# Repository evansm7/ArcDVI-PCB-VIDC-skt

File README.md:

# ArcDVI VIDC socket interposer PCB

Kicad 6.0 PCB design for the ArcDVI VIDC socket interposer board:

This board carries a PLCC68 socket on top, and PLCC68 plug on bottom.  It plugs into VIDC's socket on an Archimedes A440-like machine, with VIDC moved to the socket on top, and exports the buffered signals over FFC to the ArcDVI main PCB.

See <https://stardot.org.uk> for more info.

# License

ArcDVI is copyright 2023 Matt Evans.

This work is licensed under the Creative Commons Attribution-NonCommercial-ShareAlike 3.0 Unported License. To view a copy of this license, visit http://creativecommons.org/licenses/by-nc-sa/3.0/ or send a letter to Creative Commons, PO Box 1866, Mountain View, CA 94042, USA.

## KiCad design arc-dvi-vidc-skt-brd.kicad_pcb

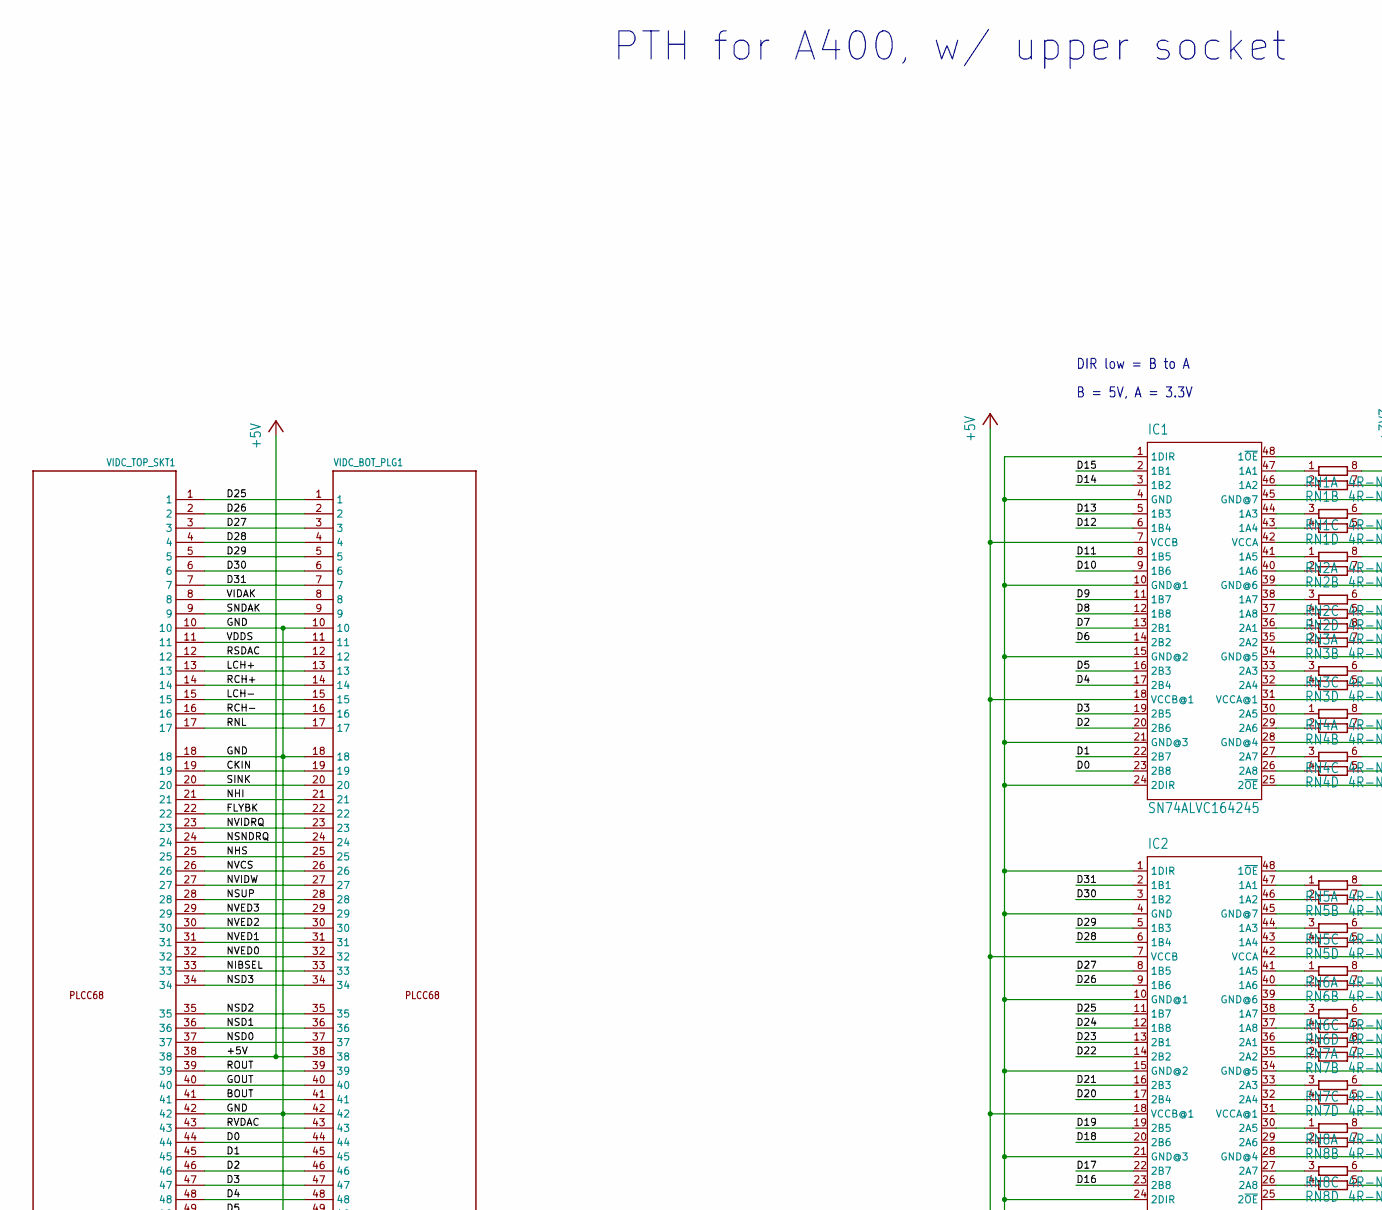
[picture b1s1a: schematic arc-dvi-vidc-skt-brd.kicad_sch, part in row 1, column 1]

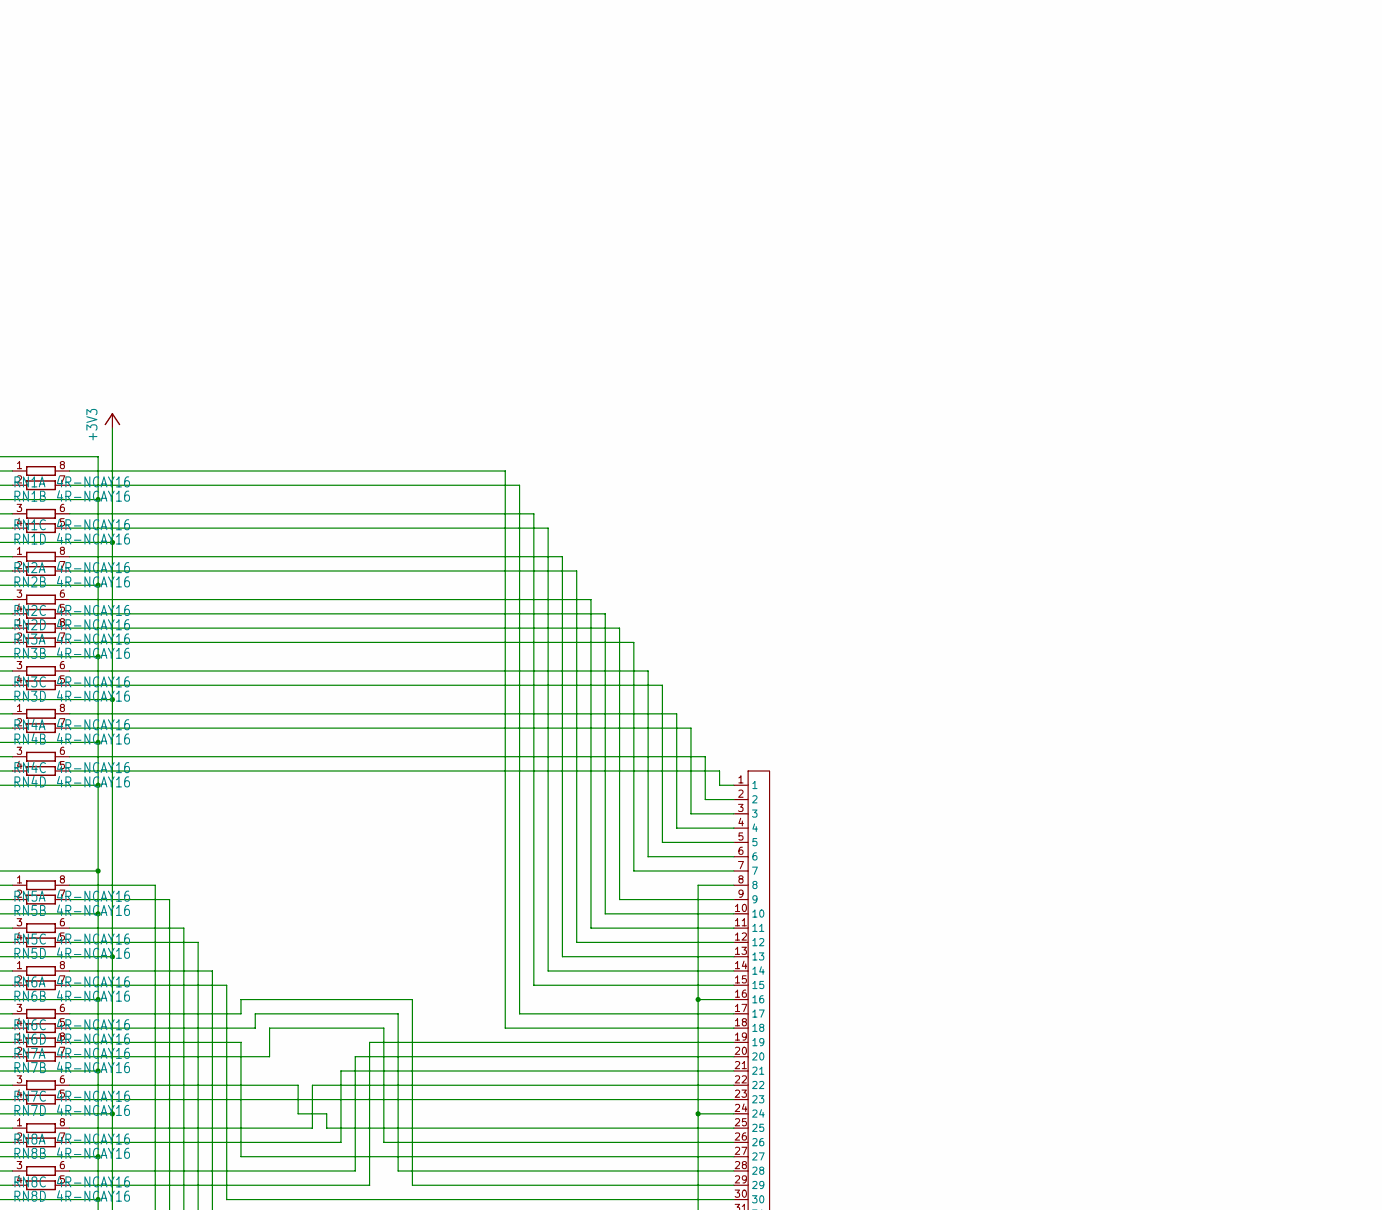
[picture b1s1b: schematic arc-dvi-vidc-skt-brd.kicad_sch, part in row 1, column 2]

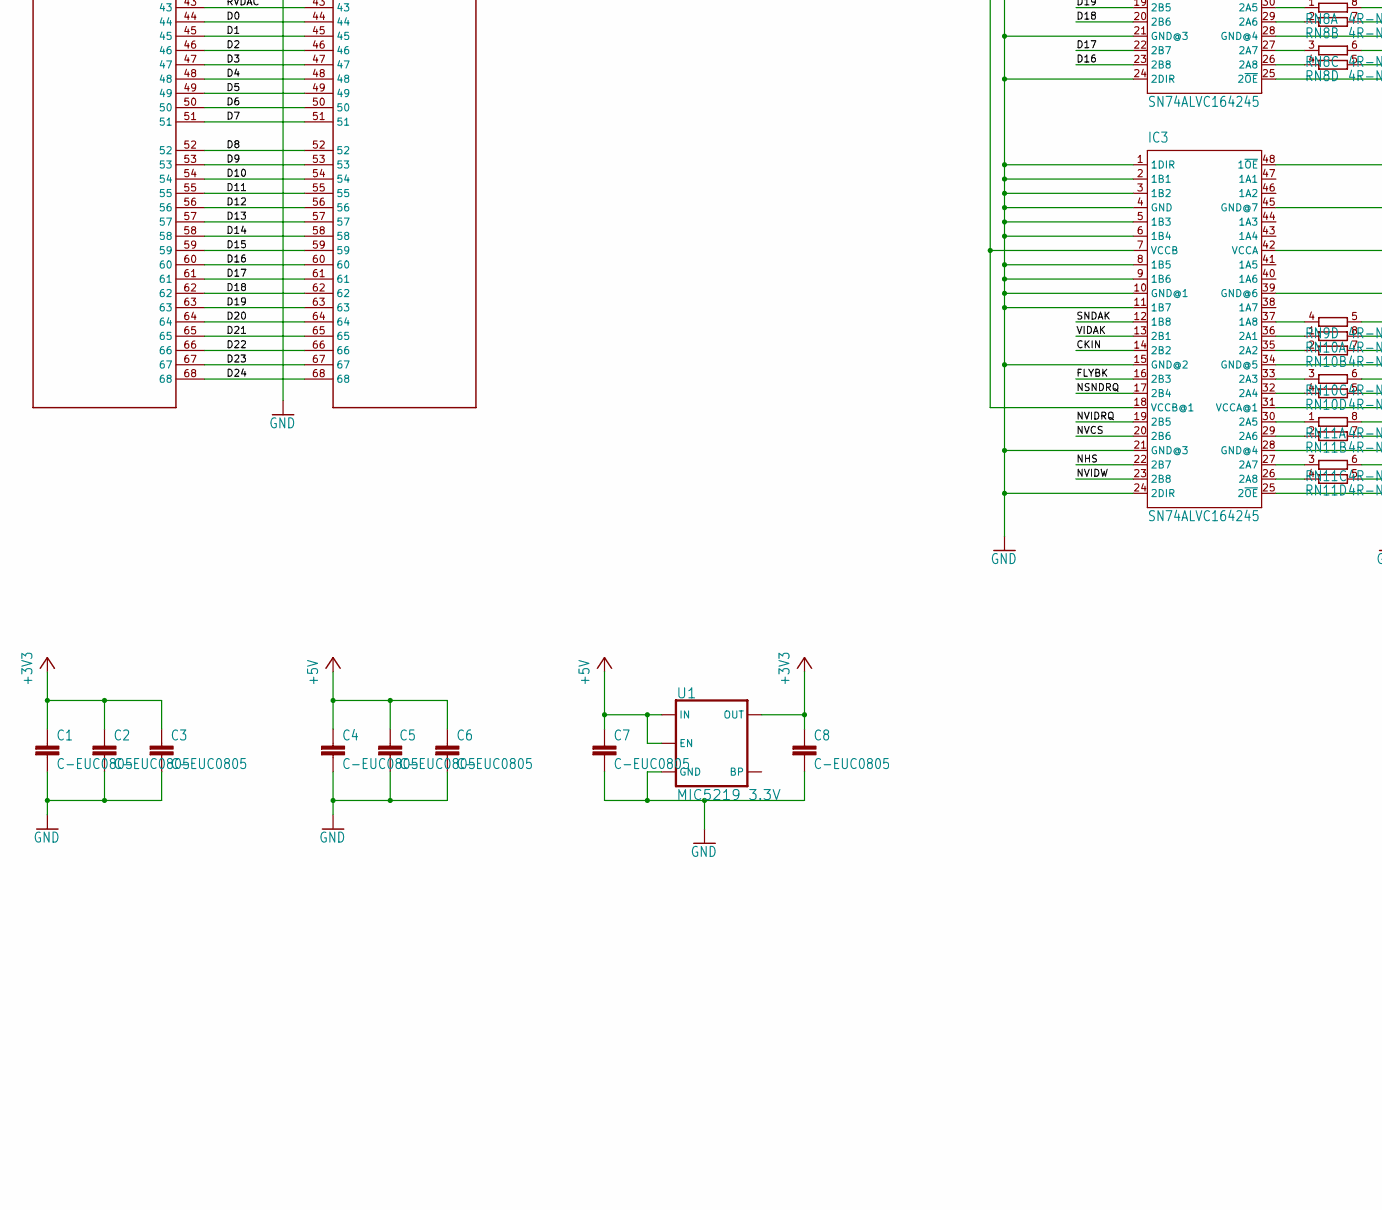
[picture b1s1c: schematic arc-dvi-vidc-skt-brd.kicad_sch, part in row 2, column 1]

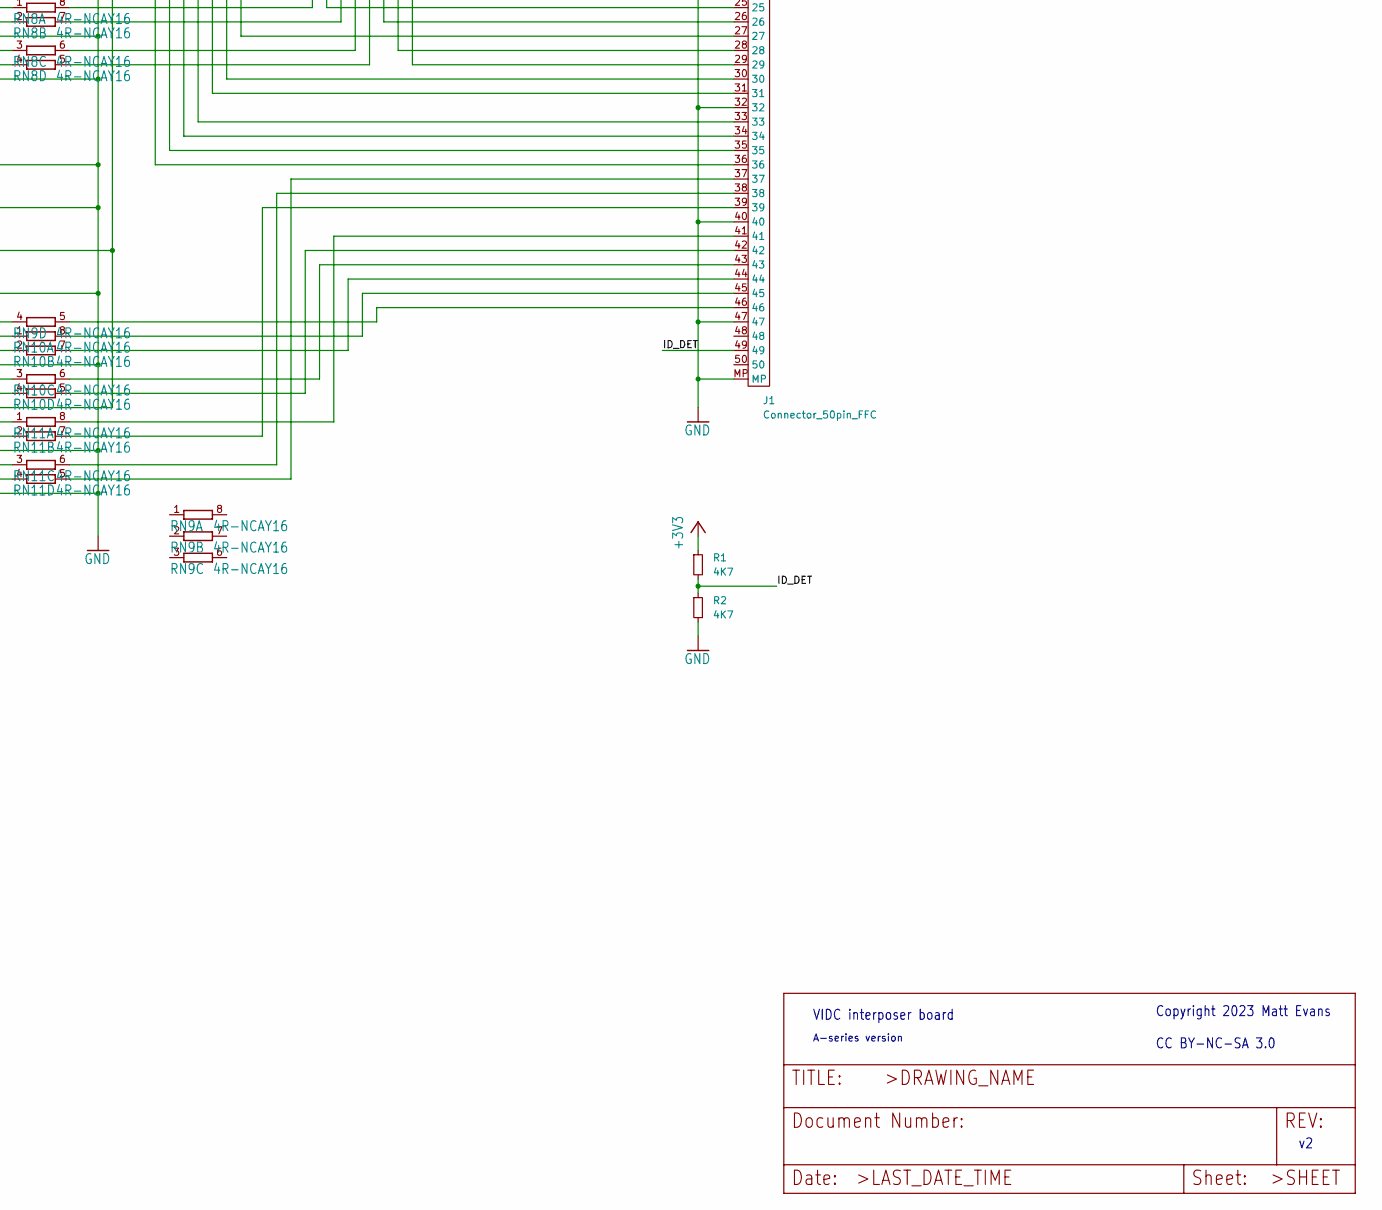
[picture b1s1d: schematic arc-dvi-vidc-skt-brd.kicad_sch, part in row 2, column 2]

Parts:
C1, C2, C3, C4, C5, C6, C7, C8: C-EUC0805; C_0805_2012Metric_Pad1.18x1.45mm_HandSolder
IC1, IC2, IC3: SN74ALVC164245; TSSOP-48_6.1x12.5mm_P0.5mm
J1: Connector_50pin_FFC; Hirose_FH12-50S-0.5SH_1x50-1MP_P0.50mm_Horizontal
R1, R2: 4K7; R_0603_1608Metric
RN1, RN2, RN3, RN4, RN5, RN6, RN7, RN8, RN9, RN10, RN11: 4R-NCAY16; R_Array_Convex_4x0603
U1: MIC5219 3.3V; SOT-23-5
VIDC_BOT_PLG1: RAW_PLCC68PTH; PLCC68-plug-wide
VIDC_TOP_SKT1: RAW_PLCC68PTH; PLCC-68_SMD-Socket

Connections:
+3V3: C1.1, C2.1, C3.1, C8.1, IC1.31 (VCCA@1), IC1.42 (VCCA), IC2.31 (VCCA@1), IC2.42 (VCCA), IC3.31 (VCCA@1), IC3.42 (VCCA), R1.1, U1.5 (OUT)
+5V: C4.1, C5.1, C6.1, C7.1, IC1.7 (VCCB), IC1.18 (VCCB@1), IC2.7 (VCCB), IC2.18 (VCCB@1), IC3.7 (VCCB), IC3.18 (VCCB@1), U1.1 (IN), U1.3 (EN), VIDC_BOT_PLG1.38, VIDC_TOP_SKT1.38
/BOUT: VIDC_BOT_PLG1.41, VIDC_TOP_SKT1.41
/CKIN: IC3.14 (2B2), VIDC_BOT_PLG1.19, VIDC_TOP_SKT1.19
/D0: IC1.23 (2B8), VIDC_BOT_PLG1.44, VIDC_TOP_SKT1.44
/D1: IC1.22 (2B7), VIDC_BOT_PLG1.45, VIDC_TOP_SKT1.45
/D2: IC1.20 (2B6), VIDC_BOT_PLG1.46, VIDC_TOP_SKT1.46
/D3: IC1.19 (2B5), VIDC_BOT_PLG1.47, VIDC_TOP_SKT1.47
/D4: IC1.17 (2B4), VIDC_BOT_PLG1.48, VIDC_TOP_SKT1.48
/D5: IC1.16 (2B3), VIDC_BOT_PLG1.49, VIDC_TOP_SKT1.49
/D6: IC1.14 (2B2), VIDC_BOT_PLG1.50, VIDC_TOP_SKT1.50
/D7: IC1.13 (2B1), VIDC_BOT_PLG1.51, VIDC_TOP_SKT1.51
/D8: IC1.12 (1B8), VIDC_BOT_PLG1.52, VIDC_TOP_SKT1.52
/D9: IC1.11 (1B7), VIDC_BOT_PLG1.53, VIDC_TOP_SKT1.53
/D10: IC1.9 (1B6), VIDC_BOT_PLG1.54, VIDC_TOP_SKT1.54
/D11: IC1.8 (1B5), VIDC_BOT_PLG1.55, VIDC_TOP_SKT1.55
/D12: IC1.6 (1B4), VIDC_BOT_PLG1.56, VIDC_TOP_SKT1.56
/D13: IC1.5 (1B3), VIDC_BOT_PLG1.57, VIDC_TOP_SKT1.57
/D14: IC1.3 (1B2), VIDC_BOT_PLG1.58, VIDC_TOP_SKT1.58
/D15: IC1.2 (1B1), VIDC_BOT_PLG1.59, VIDC_TOP_SKT1.59
/D16: IC2.23 (2B8), VIDC_BOT_PLG1.60, VIDC_TOP_SKT1.60
/D17: IC2.22 (2B7), VIDC_BOT_PLG1.61, VIDC_TOP_SKT1.61
/D18: IC2.20 (2B6), VIDC_BOT_PLG1.62, VIDC_TOP_SKT1.62
/D19: IC2.19 (2B5), VIDC_BOT_PLG1.63, VIDC_TOP_SKT1.63
/D20: IC2.17 (2B4), VIDC_BOT_PLG1.64, VIDC_TOP_SKT1.64
/D21: IC2.16 (2B3), VIDC_BOT_PLG1.65, VIDC_TOP_SKT1.65
/D22: IC2.14 (2B2), VIDC_BOT_PLG1.66, VIDC_TOP_SKT1.66
/D23: IC2.13 (2B1), VIDC_BOT_PLG1.67, VIDC_TOP_SKT1.67
/D24: IC2.12 (1B8), VIDC_BOT_PLG1.68, VIDC_TOP_SKT1.68
/D25: IC2.11 (1B7), VIDC_BOT_PLG1.1, VIDC_TOP_SKT1.1
/D26: IC2.9 (1B6), VIDC_BOT_PLG1.2, VIDC_TOP_SKT1.2
/D27: IC2.8 (1B5), VIDC_BOT_PLG1.3, VIDC_TOP_SKT1.3
/D28: IC2.6 (1B4), VIDC_BOT_PLG1.4, VIDC_TOP_SKT1.4
/D29: IC2.5 (1B3), VIDC_BOT_PLG1.5, VIDC_TOP_SKT1.5
/D30: IC2.3 (1B2), VIDC_BOT_PLG1.6, VIDC_TOP_SKT1.6
/D31: IC2.2 (1B1), VIDC_BOT_PLG1.7, VIDC_TOP_SKT1.7
/FLYBK: IC3.16 (2B3), VIDC_BOT_PLG1.22, VIDC_TOP_SKT1.22
/GOUT: VIDC_BOT_PLG1.40, VIDC_TOP_SKT1.40
/ID_DET: J1.49, R1.2, R2.1
/LCH+: VIDC_BOT_PLG1.13, VIDC_TOP_SKT1.13
/LCH-: VIDC_BOT_PLG1.15, VIDC_TOP_SKT1.15
/NHI: VIDC_BOT_PLG1.21, VIDC_TOP_SKT1.21
/NHS: IC3.22 (2B7), VIDC_BOT_PLG1.25, VIDC_TOP_SKT1.25
/NIBSEL: VIDC_BOT_PLG1.33, VIDC_TOP_SKT1.33
/NSD0: VIDC_BOT_PLG1.37, VIDC_TOP_SKT1.37
/NSD1: VIDC_BOT_PLG1.36, VIDC_TOP_SKT1.36
/NSD2: VIDC_BOT_PLG1.35, VIDC_TOP_SKT1.35
/NSD3: VIDC_BOT_PLG1.34, VIDC_TOP_SKT1.34
/NSNDRQ: IC3.17 (2B4), VIDC_BOT_PLG1.24, VIDC_TOP_SKT1.24
/NSUP: VIDC_BOT_PLG1.28, VIDC_TOP_SKT1.28
/NVCS: IC3.20 (2B6), VIDC_BOT_PLG1.26, VIDC_TOP_SKT1.26
/NVED0: VIDC_BOT_PLG1.32, VIDC_TOP_SKT1.32
/NVED1: VIDC_BOT_PLG1.31, VIDC_TOP_SKT1.31
/NVED2: VIDC_BOT_PLG1.30, VIDC_TOP_SKT1.30
/NVED3: VIDC_BOT_PLG1.29, VIDC_TOP_SKT1.29
/NVIDRQ: IC3.19 (2B5), VIDC_BOT_PLG1.23, VIDC_TOP_SKT1.23
/NVIDW: IC3.23 (2B8), VIDC_BOT_PLG1.27, VIDC_TOP_SKT1.27
/RCH+: VIDC_BOT_PLG1.14, VIDC_TOP_SKT1.14
/RCH-: VIDC_BOT_PLG1.16, VIDC_TOP_SKT1.16
/RNL: VIDC_BOT_PLG1.17, VIDC_TOP_SKT1.17
/ROUT: VIDC_BOT_PLG1.39, VIDC_TOP_SKT1.39
/RSDAC: VIDC_BOT_PLG1.12, VIDC_TOP_SKT1.12
/RVDAC: VIDC_BOT_PLG1.43, VIDC_TOP_SKT1.43
/SINK: VIDC_BOT_PLG1.20, VIDC_TOP_SKT1.20
/SNDAK: IC3.12 (1B8), VIDC_BOT_PLG1.9, VIDC_TOP_SKT1.9
/VDDS: VIDC_BOT_PLG1.11, VIDC_TOP_SKT1.11
/VIDAK: IC3.13 (2B1), VIDC_BOT_PLG1.8, VIDC_TOP_SKT1.8
GND: C1.2, C2.2, C3.2, C4.2, C5.2, C6.2, C7.2, C8.2, IC1.1 (1DIR), IC1.4 (GND), IC1.10 (GND@1), IC1.15 (GND@2), IC1.21 (GND@3), IC1.24 (2DIR), IC1.25 (2~OE), IC1.28 (GND@4), IC1.34 (GND@5), IC1.39 (GND@6), IC1.45 (GND@7), IC1.48 (1~OE), IC2.1 (1DIR), IC2.4 (GND), IC2.10 (GND@1), IC2.15 (GND@2), IC2.21 (GND@3), IC2.24 (2DIR), IC2.25 (2~OE), IC2.28 (GND@4), IC2.34 (GND@5), IC2.39 (GND@6), IC2.45 (GND@7), IC2.48 (1~OE), IC3.1 (1DIR), IC3.2 (1B1), IC3.3 (1B2), IC3.4 (GND), IC3.5 (1B3), IC3.6 (1B4), IC3.8 (1B5), IC3.9 (1B6), IC3.10 (GND@1), IC3.11 (1B7), IC3.15 (GND@2), IC3.21 (GND@3), IC3.24 (2DIR), IC3.25 (2~OE), IC3.28 (GND@4), IC3.34 (GND@5), IC3.39 (GND@6), IC3.45 (GND@7), IC3.48 (1~OE), J1.8, J1.16, J1.24, J1.32, J1.40, J1.47, J1.MP, R2.2, U1.2 (GND), VIDC_BOT_PLG1.10, VIDC_BOT_PLG1.18, VIDC_BOT_PLG1.42, VIDC_TOP_SKT1.10, VIDC_TOP_SKT1.18, VIDC_TOP_SKT1.42
unnamed: IC1.26 (2A8), RN4.4 (1)
unnamed: IC1.27 (2A7), RN4.3 (1)
unnamed: IC1.29 (2A6), RN4.2 (1)
unnamed: IC1.30 (2A5), RN4.1
unnamed: IC1.32 (2A4), RN3.4 (1)
unnamed: IC1.33 (2A3), RN3.3 (1)
unnamed: IC1.35 (2A2), RN3.2 (1)
unnamed: IC1.36 (2A1), RN3.1
unnamed: IC1.37 (1A8), RN2.4 (1)
unnamed: IC1.38 (1A7), RN2.3 (1)
unnamed: IC1.40 (1A6), RN2.2 (1)
unnamed: IC1.41 (1A5), RN2.1
unnamed: IC1.43 (1A4), RN1.4 (1)
unnamed: IC1.44 (1A3), RN1.3 (1)
unnamed: IC1.46 (1A2), RN1.2 (1)
unnamed: IC1.47 (1A1), RN1.1
unnamed: IC2.26 (2A8), RN8.4 (1)
unnamed: IC2.27 (2A7), RN8.3 (1)
unnamed: IC2.29 (2A6), RN8.2 (1)
unnamed: IC2.30 (2A5), RN8.1
unnamed: IC2.32 (2A4), RN7.4 (1)
unnamed: IC2.33 (2A3), RN7.3 (1)
unnamed: IC2.35 (2A2), RN7.2 (1)
unnamed: IC2.36 (2A1), RN7.1
unnamed: IC2.37 (1A8), RN6.4 (1)
unnamed: IC2.38 (1A7), RN6.3 (1)
unnamed: IC2.40 (1A6), RN6.2 (1)
unnamed: IC2.41 (1A5), RN6.1
unnamed: IC2.43 (1A4), RN5.4 (1)
unnamed: IC2.44 (1A3), RN5.3 (1)
unnamed: IC2.46 (1A2), RN5.2 (1)
unnamed: IC2.47 (1A1), RN5.1
unnamed: IC3.26 (2A8), RN11.4 (1)
unnamed: IC3.29 (2A6), RN11.2 (1)
unnamed: IC3.37 (1A8), RN9.4 (1)
unnamed: J1.1, RN4.5 (2)
unnamed: J1.2, RN4.6 (2)
unnamed: J1.3, RN4.7 (2)
unnamed: J1.4, RN4.8 (2)
unnamed: J1.5, RN3.5 (2)
unnamed: J1.6, RN3.6 (2)
unnamed: J1.7, RN3.7 (2)
unnamed: J1.9, RN3.8 (2)
unnamed: J1.10, RN2.5 (2)
unnamed: J1.11, RN2.6 (2)
unnamed: J1.12, RN2.7 (2)
unnamed: J1.13, RN2.8 (2)
unnamed: J1.14, RN1.5 (2)
unnamed: J1.15, RN1.6 (2)
unnamed: J1.17, RN1.7 (2)
unnamed: J1.18, RN1.8 (2)
unnamed: J1.19, RN8.5 (2)
unnamed: J1.20, RN8.6 (2)
unnamed: J1.21, RN8.7 (2)
unnamed: J1.22, RN8.8 (2)
unnamed: J1.23, RN7.5 (2)
unnamed: J1.25, RN7.6 (2)
unnamed: J1.26, RN7.7 (2)
unnamed: J1.27, RN7.8 (2)
unnamed: J1.28, RN6.5 (2)
unnamed: J1.29, RN6.6 (2)
unnamed: J1.30, RN6.7 (2)
unnamed: J1.31, RN6.8 (2)
unnamed: J1.33, RN5.5 (2)
unnamed: J1.34, RN5.6 (2)
unnamed: J1.35, RN5.7 (2)
unnamed: J1.36, RN5.8 (2)
unnamed: J1.37, RN11.5 (2)
unnamed: J1.46, RN9.5 (2)
unnamed: IC3.36 (2A1), RN10.1
unnamed: IC3.35 (2A2), RN10.2 (1)
unnamed: IC3.33 (2A3), RN10.3 (1)
unnamed: IC3.32 (2A4), RN10.4 (1)
unnamed: J1.42, RN10.5 (2)
unnamed: J1.43, RN10.6 (2)
unnamed: J1.44, RN10.7 (2)
unnamed: J1.45, RN10.8 (2)
unnamed: IC3.30 (2A5), RN11.1
unnamed: IC3.27 (2A7), RN11.3 (1)
unnamed: J1.38, RN11.6 (2)
unnamed: J1.39, RN11.7 (2)
unnamed: J1.41, RN11.8 (2)

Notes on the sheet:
VIDC interposer board
A-series version
B = 5V, A = 3.3V
PTH for A400, w/ upper socket
DIR low = B to A
Copyright 2023 Matt Evans CC BY-NC-SA 3.0

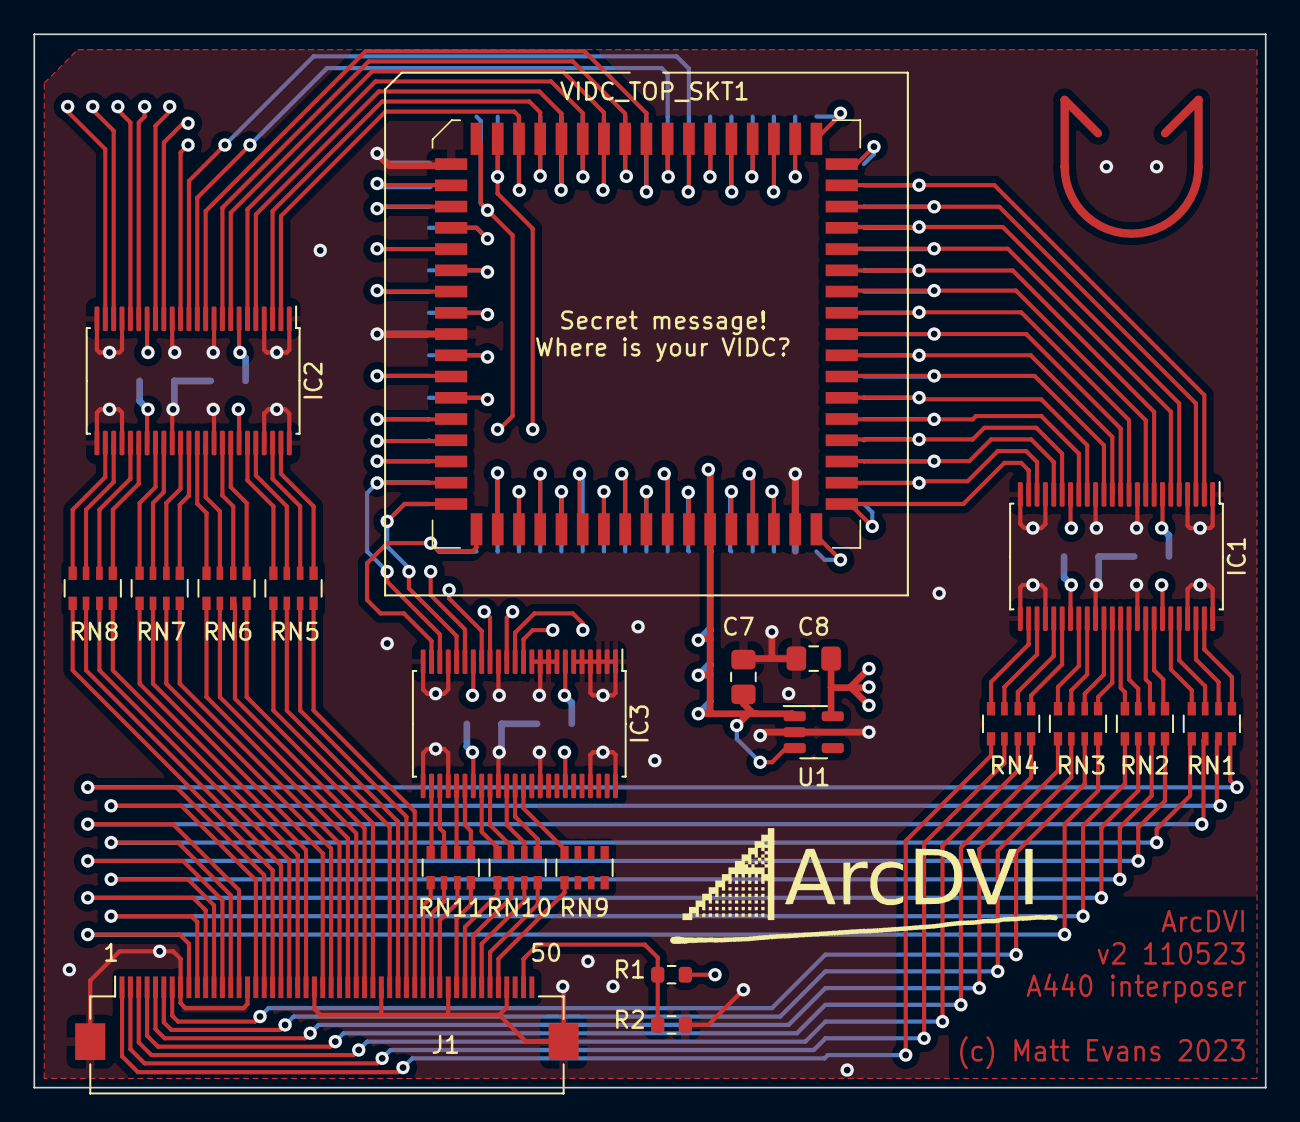
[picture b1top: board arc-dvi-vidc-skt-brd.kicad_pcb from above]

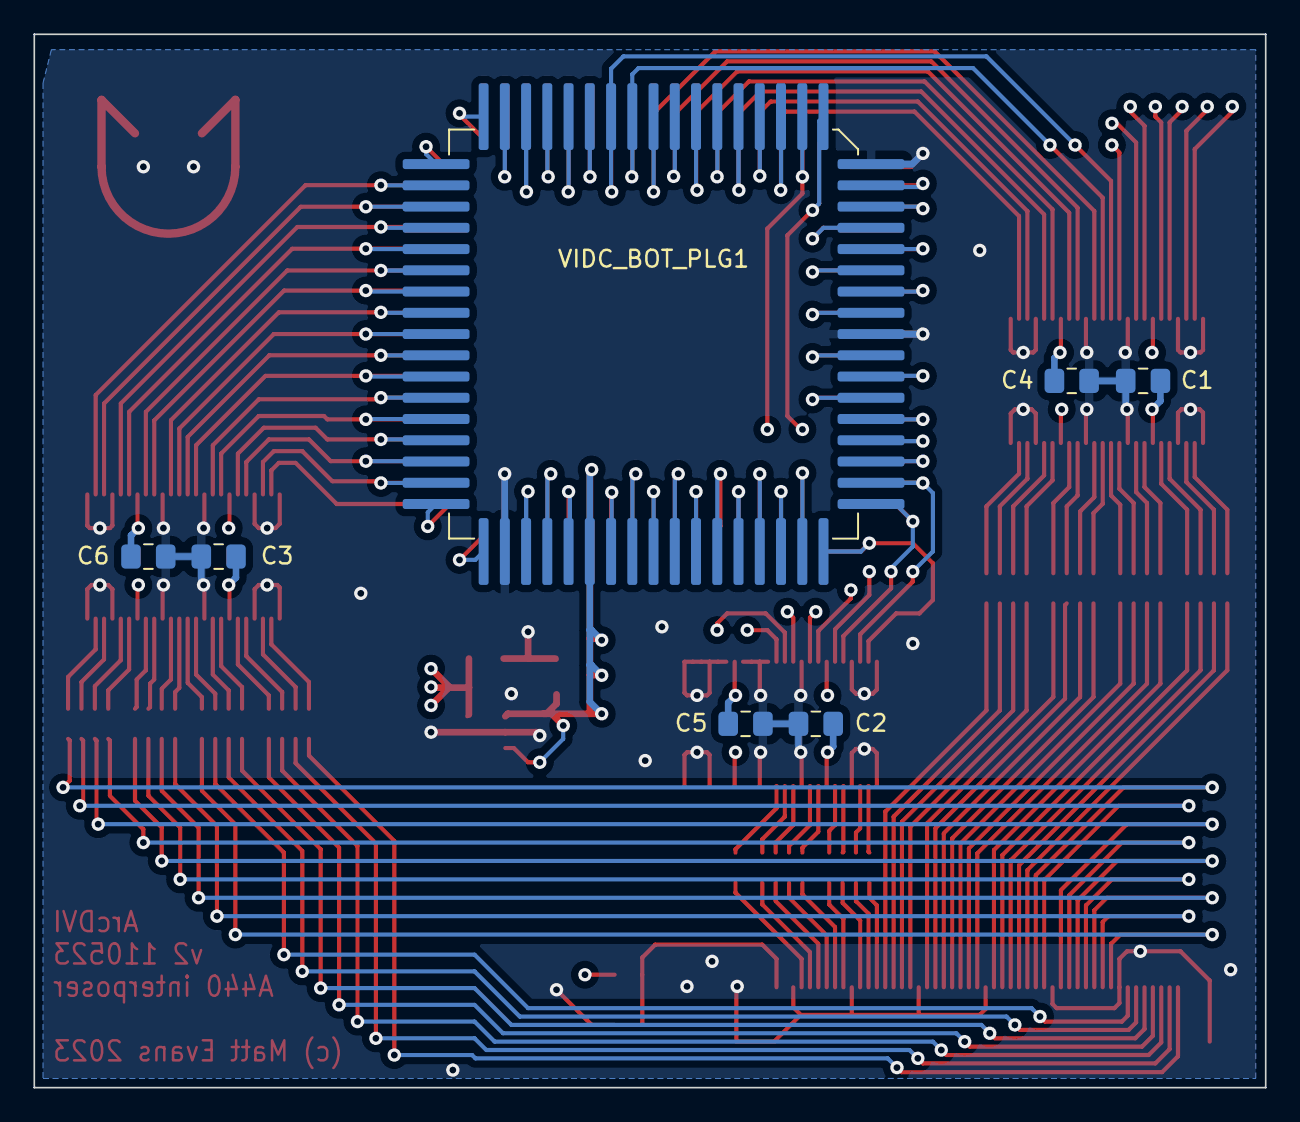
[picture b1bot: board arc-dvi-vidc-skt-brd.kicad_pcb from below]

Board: 4 copper layers, 73.6 x 63.0 mm, 28 parts (6 on the bottom side), 150 nets.

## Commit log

2023-03-09 First board, with PLCC68 plug and top socket
    Derived from non-interposer version
2023-05-08 Placed, partially routed
    Same schematic as A3000 arc-dvi-vidc-brds, same FFC pinout (yay).
2023-05-10 Routed, passes DRC
    Candidate! V2
2023-05-11 Final tweaks for aesthetics
2023-05-14 Add logo, final silkscreen tweak
2023-06-01 Aesthetic: Moved bot silk refdes
2023-06-11 Add README, image, licence
2023-06-11 Remove sym-lib-table
